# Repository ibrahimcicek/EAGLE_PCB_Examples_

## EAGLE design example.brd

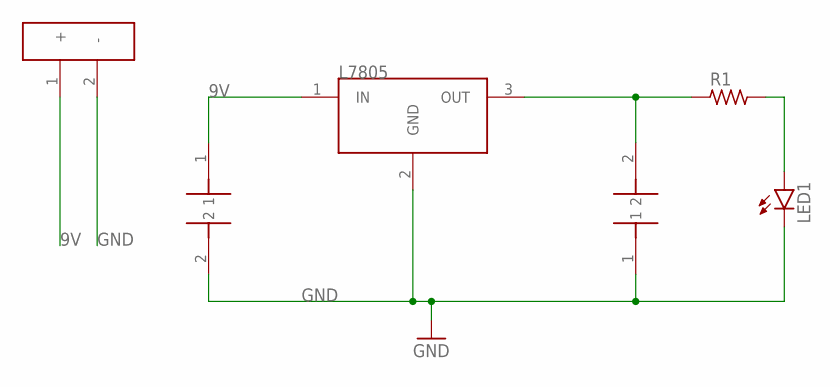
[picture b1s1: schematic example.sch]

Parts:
LED1: LEDCHIP-LED0805; CHIP-LED0805
R1: R_1206; R1206
U$1: L7805A; L7805
U$2: 2X1KLAMENSA; 2X1KLAMENS
U$3: 0.1UF; C1206
U$4: 0.33UF; C1206

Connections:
9V: U$1.1 (IN), U$2.1 (+), U$3.1
GND: LED1.C, U$1.2 (GND), U$2.2 (-), U$3.2, U$4.1
unnamed: R1.1, U$1.3 (OUT), U$4.2
unnamed: LED1.A, R1.2

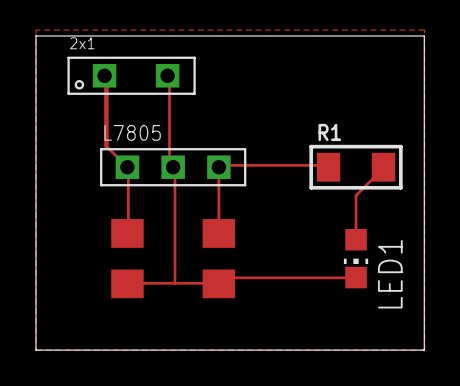
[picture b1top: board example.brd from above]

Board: 2 copper layers, 21.6 x 17.4 mm, 6 parts (0 on the bottom side), 4 nets.

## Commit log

2021-07-06 Create example_regulator_lib.l##
2021-07-06 Create example_regulator_lib.l#1
2021-07-06 Create example_regulator_lib.l#2
2021-07-06 Create example_regulator_lib.l#3
2021-07-08 Update example_regulator_lib.l#1
2021-07-08 Update example_regulator_lib.l#2
2021-07-08 Update example_regulator_lib.l#3
2021-07-08 Create example_regulator_lib.l#4
2021-07-08 Update example_regulator_lib.l#4
2021-07-08 Create example_regulator_lib.l#5
2021-07-08 Create example_regulator_lib.l#6
2021-07-08 Create example_regulator_lib.l#9
2021-07-08 Create example_regulator_lib.l#8
2021-07-08 Create example_regulator_lib.l#7
2021-07-08 Update example_regulator_lib.l#6
2021-07-08 Update example_regulator_lib.l#5
2021-07-08 Create example.s#1

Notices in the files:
parts and their libraries:
cap_master-smd: Copyright (C) 2007, Bob Starr
